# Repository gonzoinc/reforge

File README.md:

# Reforge

First-generation Reforge Basic and Advanced climate-control display conversions are **open for preorder** for compatible 1991–1997 Mitsubishi 3000GT and Dodge Stealth vehicles with digital climate control. Reforge is a mail-in conversion service, not a self-install kit. The factory climate-control computer and controls remain in place.

| Version | Best for | Preorder |
| --- | --- | --- |
| **Basic** | A fixed OEM-style display of live factory climate information. | [Preorder Basic](https://reforge.gonzoinc.com/product/reforge-1st-gen-climate-control-basic-preorder-deposit/) |
| **Advanced** | Custom templates, app uploads, touchscreen settings, screensavers, and plugin support. | [Preorder Advanced](https://reforge.gonzoinc.com/product/reforge-1st-gen-climate-control-advanced-preorder-deposit/) |

Each preorder requires a **$100 non-refundable deposit per unit**, credited toward the final conversion price. The current conversion prices are $500 for Basic and $575 for Advanced, before selected add-ons and return shipping. Preorders close **November 15, 2026 at 11:59 PM Eastern**. Read the product pages for compatibility, options, timing, and the full deposit terms. **Do not mail your unit with the deposit**; shipping instructions follow final payment.

The [Reforge website](https://reforge.gonzoinc.com/) is the source for current product and ordering information. This repository provides Windows app downloads, documentation, and app issue tracking. The available app installers and firmware packages have their own release status; a release labeled beta or alpha is still an early software build.

<h3 align="center">Connecting legacy to tomorrow.</h3>

<p align="center">
  <a href="https://reforge.gonzoinc.com/"><strong>🌐 Visit the Reforge website</strong></a>
  &nbsp; • &nbsp;
  <a href="https://www.facebook.com/reforge3s/"><strong>📣 Follow Reforge on Facebook</strong></a>
  &nbsp; • &nbsp;
  <a href="https://github.com/gonzoinc/reforge/issues"><strong>🐛 Report an app bug</strong></a>
</p>

## Windows App and Firmware Downloads

Browse the [official Releases page](https://github.com/gonzoinc/reforge/releases) for the Windows installer, firmware packages, checksums, and release notes. Check each release's version, requirements, and limitations before installing. Verify downloaded files against their published SHA-256 checksums.

The installer is unsigned. Follow the [SmartScreen instructions below](#installing-unsigned-reforge-builds-on-windows) if Windows blocks a verified download. The app can update **Advanced** firmware over USB; Basic needs a separate compatible flashing workflow.

> [!IMPORTANT]
> Preordering a first-generation conversion does not change the status of individual app or firmware releases. Check the notes for the specific download you use. Software build checks alone do not establish hardware acceptance.

Reforge is a Windows desktop application for creating, managing, and uploading display templates for supported Mitsubishi 3000GT and Dodge Stealth digital climate-control display replacements.

- 🎨 Create and customize display templates.
- 🧩 Manage artwork, layouts, and display assets.
- 🚀 Upload finished templates to supported Reforge displays over USB or Bluetooth.

## 🔧 Basic and Advanced Display Versions

Two Reforge display versions are available to preorder as first-generation mail-in conversions. Both replace the original display and show live factory climate-control information, but they offer different levels of customization. The current preorder is for a conversion service, not a retail display or a self-install kit.

> [!IMPORTANT]
> A 1st-gen DCC does not automatically include the Advanced features. Custom templates, multiple template slots, app/USB/Bluetooth template uploads, touchscreen settings, user-adjustable and automatic dimming, screensavers, and plugins require the **1st-gen DCC Advanced Version**. The 1st-gen DCC Basic Version does not support those features.

| Feature | 1st-gen Basic Version | 1st-gen Advanced Version |
| --- | :---: | :---: |
| Designed for the 1st-gen DCC | ✅ | ✅ |
| Live temperature, fan, vent mode, A/C, AUTO, ECON, and intake status | ✅ | ✅ |
| 3.5-inch 480 × 320 color display | ✅ | ✅ |
| Built-in Reforge `1st Gen OEM DCC` display layout | ✅ | ✅ |
| Dims with the vehicle illumination signal | ✅ | ✅ |
| User-adjustable brightness and automatic dimming | ❌ | ✅ |
| Custom display templates | ❌ | ✅ |
| Multiple template slots | ❌ | ✅ |
| Template upload from the Reforge app | ❌ | ✅ |
| USB template upload | ❌ | ✅ |
| Bluetooth template upload | ❌ | ✅ |
| Touchscreen menu and settings | ❌ | ✅ |
| Screensaver support | ❌ | ✅ |
| Reforge plugin support | ❌ | ✅ |
| Passive CAN and digital-input plugins | ❌ | ✅ |

### Basic

Basic is the simple OEM-style version. It starts directly into the built-in `1st Gen OEM DCC` layout and displays the normal climate-control information. It has no custom templates, template uploads, Bluetooth service, touchscreen menu, screensaver, user settings, or plugins. Display brightness switches between fixed normal and dim levels using the vehicle illumination signal.

### Advanced

The **1st-gen DCC Advanced Version** is the customizable 1st-gen product. It supports Reforge templates, two on-device template slots, app/USB/Bluetooth template uploads, touchscreen controls, persistent brightness and automatic dim/black settings, screensavers, and Plugin API v1. The 1st-gen DCC Basic Version does not support those features. Plugin API v1 also does not support 2nd-gen DCC boards.

See [Building Reforge Plugins](plugin.md) for the package format, available inputs, manifest examples, and current development status.

Complete examples are available in the [reference plugins folder](plugins/README.md), including the configurable [Reforge CAN Mapper](plugins/can-mapper/README.md).

> [!NOTE]
> Advanced plugin support remains limited to the **1st-gen DCC Advanced Version**. Firmware export and live on-device plugin data are not complete yet.

> [!TIP]
> 📣 **Follow [Reforge on Facebook](https://www.facebook.com/reforge3s/) for project updates and release news.** Visit [reforge.gonzoinc.com](https://reforge.gonzoinc.com/) for current preorder information.

> [!WARNING]
> App and firmware prereleases may contain bugs or incomplete features. Review the notes for the version you download.

## About This Repository

This repository is the public home for:

- Official compiled Reforge app and firmware downloads.
- End-user information and release notes.
- App bug reports and issue tracking.
- License, notices, and branding terms.

Application source code, firmware source code, hardware designs, PCB files, manufacturing files, and private development material are **not published in this repository**.

## 🖥️ System Requirements

- Windows 10 or Windows 11, 64-bit.
- The installer includes the required .NET desktop runtime; a separate .NET installation is not required.

## 📦 Downloading Reforge

1. Open [Releases](https://github.com/gonzoinc/reforge/releases).
2. Choose the Windows app release appropriate for your display and review its notes. Basic and Advanced firmware have separate release pages.
3. Download the Windows installer attached to the selected release.
4. Compare the installer’s SHA-256 hash with the published checksum before running it.

## 🛡️ Installing Unsigned Reforge Builds on Windows

Reforge installers are not code-signed. On some Windows systems, Microsoft Defender SmartScreen blocks the installer completely and does not offer a **Run anyway** option. In that case, SmartScreen's app check must be disabled temporarily before the installer can run.

Before changing SmartScreen:

1. Confirm that the installer came from this repository's [official Releases page](https://github.com/gonzoinc/reforge/releases).
2. Compare the downloaded installer's SHA-256 hash with the checksum published beside that release.
3. Do not continue if the filename or checksum does not match.

To install when SmartScreen blocks the file:

1. Open **Windows Security** from the Windows Start menu.
2. Select **App & browser control**.
3. Select **Reputation-based protection settings**.
4. Turn **Check apps and files** off. Approve the Windows confirmation prompt if one appears.
5. Run the Reforge installer again.
6. Windows will still display a confirmation warning because the installer has an unknown publisher. Select the affirmative option—such as **Yes**, **Run**, or **Proceed**—to continue the installation.
7. As soon as installation finishes, return to **Windows Security → App & browser control → Reputation-based protection settings** and turn **Check apps and files** back on.

> [!IMPORTANT]
> Disable only **Check apps and files**, only for the time needed to install the verified Reforge download, and re-enable it immediately afterward. Do not disable antivirus protection or other Windows Security features. If a work or school administrator controls this setting, contact that administrator instead of bypassing the policy.

See Microsoft's [App & browser control documentation](https://support.microsoft.com/en-us/windows/app-browser-control-in-the-windows-security-app-8f68fb65-ebb4-3cfb-4bd7-2a32ea6bd946) for additional information about SmartScreen and reputation-based protection.

## 🐛 Reporting an App Bug

Use the [Reforge app bug form](https://github.com/gonzoinc/reforge/issues/new?template=bug-report.yml). The form asks for the app version, affected area, Windows version, steps to reproduce the problem, and any useful screenshots or logs.

Before filing a report:

- Check [existing issues](https://github.com/gonzoinc/reforge/issues) for the same problem.
- Remove passwords, access tokens, private keys, personal information, and other secrets from screenshots or logs.
- Report only Reforge desktop-app problems here. Firmware, hardware, wiring, installation, and vehicle issues are outside this repository’s current bug-tracking scope.

The app’s yellow bug button opens the repository’s Issues page in the default web browser.

## ⚖️ License

Official Reforge app binaries are licensed for personal, educational, repair, hobby, research, and other noncommercial use under the [PolyForm Noncommercial License 1.0.0](LICENSE.md), subject to the required notices in that file.

Commercial use is not included. See [Commercial Licensing](COMMERCIAL-LICENSE.md) for examples and additional information.

The license does not grant access to or rights in unpublished source code, firmware source, hardware designs, PCB files, manufacturing data, trademarks, logos, or branding.

## 📚 Legal And Project Documents

- [Plugin Authoring Guide](plugin.md)
- [Software License](LICENSE.md)
- [Notices](NOTICE.md)
- [Commercial Licensing](COMMERCIAL-LICENSE.md)
- [Bug Reports and Contributions](CONTRIBUTING.md)
- [Security Policy](SECURITY.md)
- [Trademarks and Branding](TRADEMARKS.md)

## ℹ️ Independence Notice

Reforge is an independent project and is not affiliated with, sponsored by, or endorsed by Mitsubishi, Dodge, Stellantis, or any related trademark holder. Third-party names are used only to identify compatibility and source-hardware context.

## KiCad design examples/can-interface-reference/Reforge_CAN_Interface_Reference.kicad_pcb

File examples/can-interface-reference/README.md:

# CAN Mapper interface reference

> [!WARNING]
> **Untested reference design only.** This circuit and PCB have not been built, bench-tested, or validated in a vehicle. They are provided as an editable KiCad example for experienced users. Do not treat this project as a finished product or a production-ready automotive design.

This example shows one simple way to connect an existing CAN bus and a nominal 12 V supply to the Reforge CAN Mapper plugin. It uses individual components rather than a prebuilt module and matches the plugin's current expansion assignments:

- Reforge connector pin 1 / `EXP_IO1`: CAN receive (`twai.rx`)
- Reforge connector pin 2 / `EXP_IO2`: controller transmit pin held recessive for listen-only operation (`twai.listen.txIdle`)
- Reforge connector pin 3 / `EXP_IO3`: not connected
- Reforge connector pin 4 / `EXP_GND`: shared logic ground

The project targets only the **1st-gen DCC Advanced Rev B 1.0** board. Basic, Advanced Rev A, and 2nd-gen boards are not supported.

## Included files

- `Reforge_CAN_Interface_Reference.zip` - downloadable bundle of the editable project and reference files
- `Reforge_CAN_Interface_Reference.kicad_pro` - KiCad project
- `Reforge_CAN_Interface_Reference.kicad_sch` - complete schematic
- `Reforge_CAN_Interface_Reference.kicad_pcb` - routed two-layer PCB
- `BOM.csv` - example bill of materials
- `Reforge_CAN_Interface_Reference.pdf` - schematic preview
- `Reforge_CAN_Interface_Reference.svg` - schematic preview
- `Reforge_CAN_Interface_Reference_PCB.svg` - top-side PCB/copper preview
- `Reforge_CAN_Interface_Reference_PCB.png` - 3D board preview

Open `Reforge_CAN_Interface_Reference.kicad_pro` in KiCad 10 or later to inspect or modify the design.

The schematic symbols and PCB footprints are embedded in the design files. The footprints reference the standard KiCad 10 component models through `KICAD10_3DMODEL_DIR`. Install KiCad's standard 3D model packages if the components do not appear in the 3D Viewer.

## Input connector J1

| Pin | Signal | Connection |
| ---: | --- | --- |
| 1 | `CAN_L` | Existing CAN bus low |
| 2 | `CAN_H` | Existing CAN bus high |
| 3 | `+12V` | Nominal 12 V supply input |
| 4 | `GND` | Supply/CAN reference ground |

Verify the source vehicle's CAN pinout and polarity before connecting it. This example assumes a common ground and is not isolated.

## Reforge connector J2

J2 is a four-position, right-angle **JST GH 1.25 mm** connector (`SM04B-GHS-TB`). It matches the connector family used on Reforge boards; it is not a generic 2.54 mm pin header.

| Pin | Reforge signal | Circuit connection |
| ---: | --- | --- |
| 1 | `EXP_IO1` / GPIO18 | SN65HVD230 receiver output (`R`) |
| 2 | `EXP_IO2` / GPIO15 | SN65HVD230 driver input (`D`), pulled up to 3.3 V |
| 3 | `EXP_IO3` / GPIO7 | Not connected |
| 4 | `EXP_GND` | Circuit ground |

The four-pin Reforge connector does not supply accessory power. This reference board derives its own 3.3 V rail from the separate 12 V input on J1.

## Termination jumper JP1

JP1 controls the onboard 120 ohm resistor:

- **Jumper open:** no termination is added. Use this when attaching to an already terminated CAN bus at a non-endpoint location.
- **Jumper installed:** R2 places 120 ohms between CAN-H and CAN-L. Use this only when the reference board is located at a bus end that needs termination.

Do not add a third 120 ohm terminator to a normally terminated bus. With vehicle power off, a healthy bus with two 120 ohm end terminators commonly measures about 60 ohms between CAN-H and CAN-L.

## How it works

U1 is a fixed 3.3 V MCP1799 high-voltage-input linear regulator. C1 and C2 provide the regulator input and output capacitance. U2 is a 3.3 V SN65HVD230 CAN transceiver, with C3 placed across its supply.

The SN65HVD230 receiver output feeds `EXP_IO1`. Its driver input is connected to the host-owned `EXP_IO2` signal and pulled high by R1 so it defaults to the recessive state. The current CAN Mapper plugin configures the controller for listen-only operation. This circuit is therefore intended for passive monitoring, but it is not a physical transmit-disable circuit; correct listen-only firmware behavior is still required.

The SN65HVD230 `RS` pin is tied low for high-speed operation. R2 and JP1 provide optional bus termination.

## Important limitations

This intentionally simple reference omits features that may be required for a reliable vehicle installation, including:

- input fuse or resettable fuse
- reverse-polarity protection
- load-dump and surge protection
- CAN-bus TVS protection or common-mode filtering
- galvanic isolation
- connector strain relief, enclosure, conformal coating, and environmental sealing
- thermal validation across vehicle voltage and temperature ranges
- electromagnetic compatibility testing

The MCP1799 can accept the nominal 12 V input used here, but a linear regulator dissipates the input-to-output voltage difference as heat. Confirm the real supply range, current draw, package temperature, capacitor voltage ratings, and fault behavior before building or installing a derivative. Review the [TI SN65HVD230 datasheet](https://www.ti.com/lit/ds/symlink/sn65hvd230.pdf) and [Microchip MCP1799 datasheet](https://ww1.microchip.com/downloads/en/DeviceDoc/MCP1799-Data-Sheet-20006248A.pdf) before selecting parts or changing the circuit.

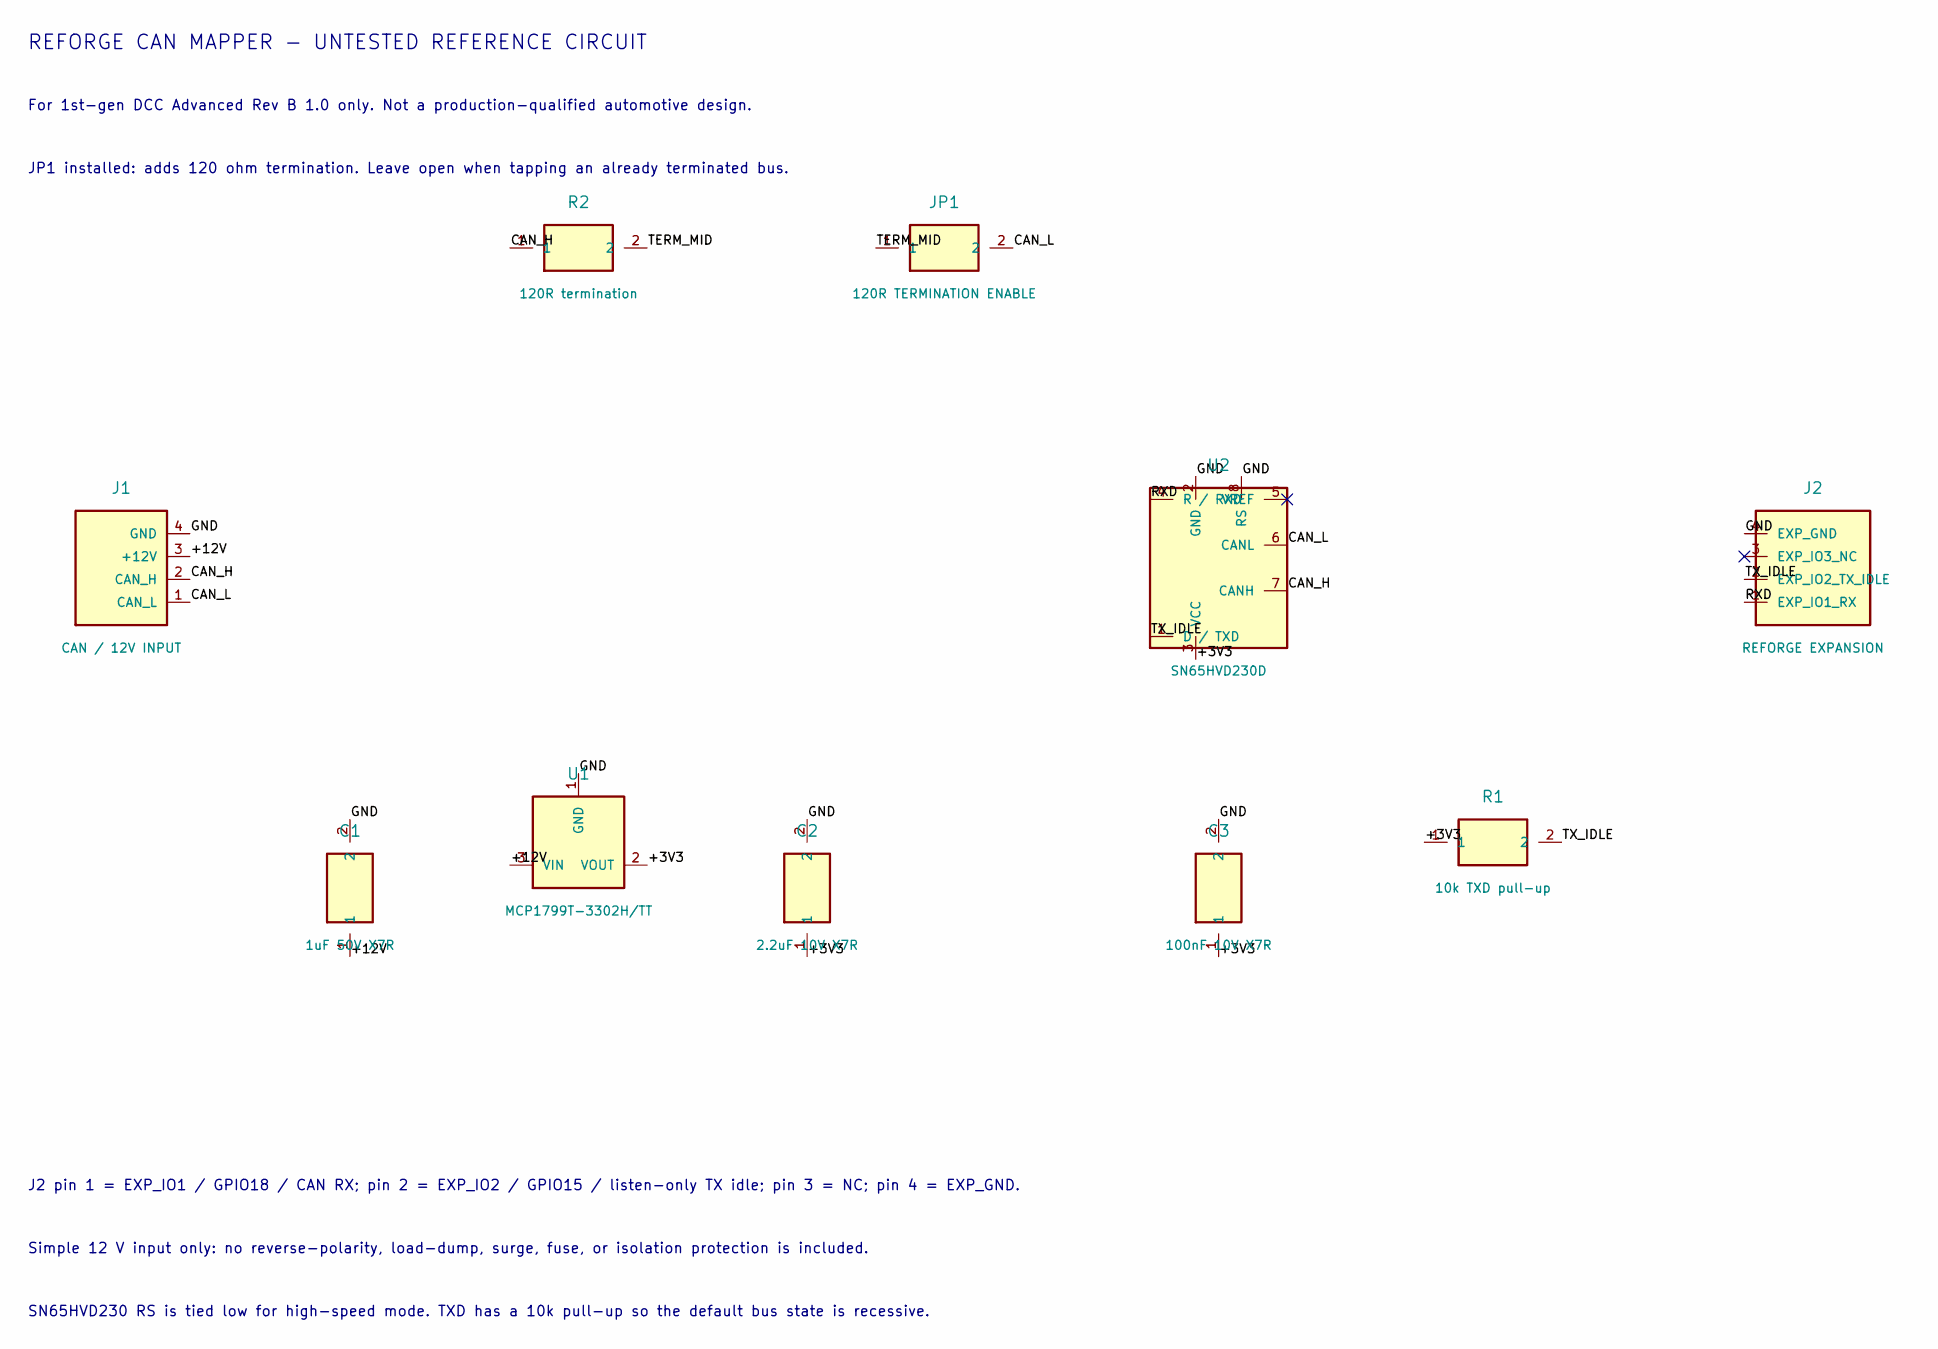
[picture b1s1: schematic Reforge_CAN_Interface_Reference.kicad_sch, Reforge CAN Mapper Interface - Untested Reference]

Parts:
C1: 1uF 50V X7R; C_0805_2012Metric
C2: 2.2uF 10V X7R; C_0805_2012Metric
C3: 100nF 10V X7R; C_0805_2012Metric
J1: CAN / 12V INPUT; TerminalBlock_Phoenix_MKDS-1,5-4-5.08_1x04_P5.08mm_Horizont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
J2: REFORGE EXPANSION; PinHeader_1x04_P2.54mm_Vertical
JP1: 120R TERMINATION ENABLE; PinHeader_1x02_P2.54mm_Vertical
R1: 10k TXD pull-up; R_0805_2012Metric
R2: 120R termination; R_0805_2012Metric
U1: MCP1799T-3302H/TT; SOT-23-3
U2: SN65HVD230D; SOIC-8_3.9x4.9mm_P1.27mm

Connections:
+3V3: C2.1, C3.1, R1.1, U1.2, U2.3
+12V: C1.1, J1.3, U1.3
CAN_H: J1.2, R2.1, U2.7
CAN_L: J1.1, JP1.2, U2.6
GND: C1.2, C2.2, C3.2, J1.4, J2.4, U1.1, U2.2, U2.8
RXD: J2.1, U2.4
TERM_MID: JP1.1, R2.2
TX_IDLE: J2.2, R1.2, U2.1

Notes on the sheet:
REFORGE CAN MAPPER - UNTESTED REFERENCE CIRCUIT
For 1st-gen DCC Advanced Rev B 1.0 only. Not a production-qualified automotive design.
JP1 installed: adds 120 ohm termination. Leave open when tapping an already terminated bus.
J2 pin 1 = EXP_IO1 / GPIO18 / CAN RX; pin 2 = EXP_IO2 / GPIO15 / listen-only TX idle; pin 3 = NC; pin 4 = EXP_GND.
Simple 12 V input only: no reverse-polarity, load-dump, surge, fuse, or isolation protection is included.
SN65HVD230 RS is tied low for high-speed mode. TXD has a 10k pull-up so the default bus state is recessive.

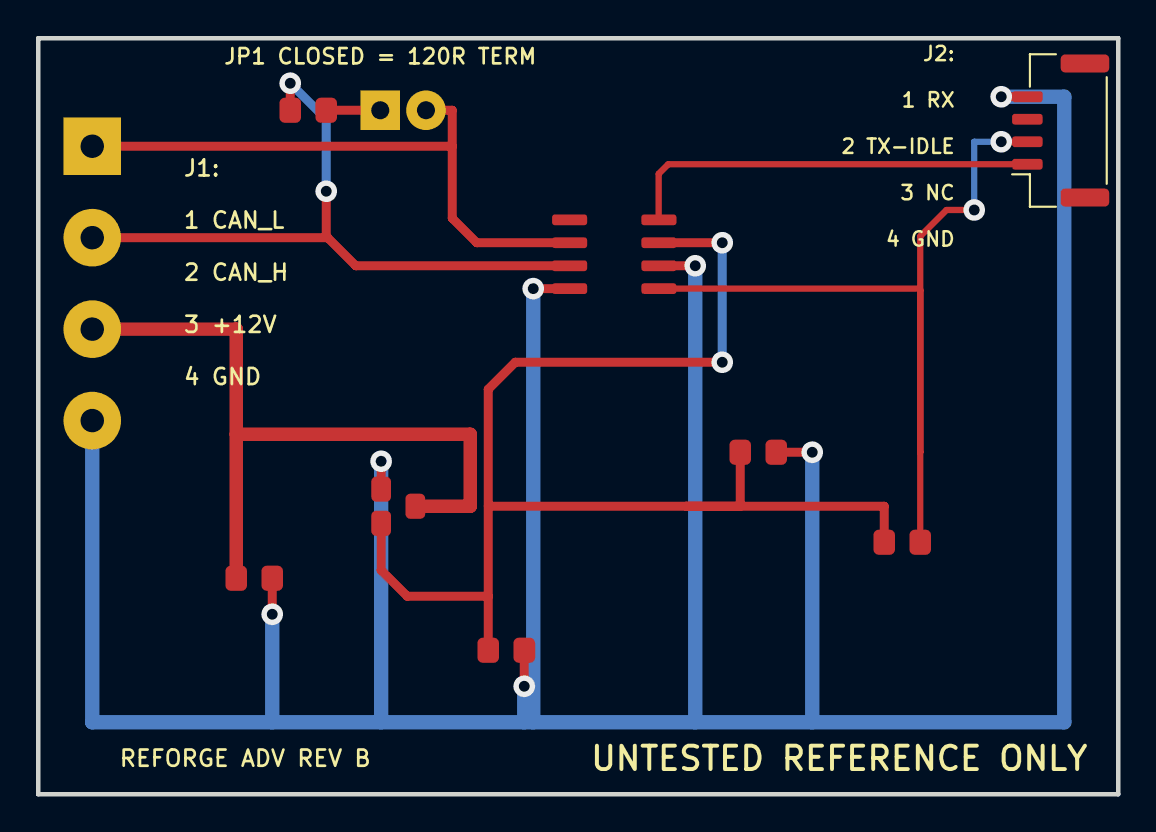
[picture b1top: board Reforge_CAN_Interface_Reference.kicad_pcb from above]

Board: 2 copper layers, 60.0 x 42.0 mm, 10 parts (0 on the bottom side), 8 nets.

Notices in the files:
README.md:
License: PolyForm Noncommercial
